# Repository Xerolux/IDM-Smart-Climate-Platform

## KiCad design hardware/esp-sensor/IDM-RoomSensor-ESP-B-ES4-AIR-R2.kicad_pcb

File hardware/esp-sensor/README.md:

# IDM Room Sensor ESP

The newest manufacturing revision is **B-ES5-MODULAR**, a 130 x 100 mm
four-layer engineering sample. It keeps ESP32-C6-N16, SHT45, USB-C, 24 V,
isolated RS-485, 0-10 V input/output, 1-Wire and contact inputs on the base and
moves CO2, VOC/NOx and pressure onto three universal 25 x 25 mm AIR-SLOT
modules. The symmetric 2x4 connector is electrically safe after 180-degree
rotation and each module has its own 3.3 V regulator.

**B-ES4-AIR-R2 Ultimate** is the all-sensors-fitted revision. It adds a
protected 6-32 VDC input rating, individually switchable LEDs and a
potential-free COM/NO/NC signal relay while retaining USB-C power/programming.
USB and external DC may be connected simultaneously through separate
Schottky OR-ing diodes. **B-ES5-MODULAR** remains intended for product tiers,
later upgrades and field-replaceable sensor modules.

Revision **B-ES2-C6** is the smaller baseline engineering
sample using an ESP32-C6-WROOM-1-N16, native USB-C, SHT45, MCP4725/OPA197
0-10 V output and isolated CA-IS3092W RS-485. It accepts protected 24 V field
power and USB power simultaneously through separate Schottky OR-ing diodes.

Revision **B-ES1** remains the simpler ESP32-C3-DevKitM-1 bench-test version.

## Order files

- B-ES5 complete package: `manufacturing/B-ES5-MODULAR/`
- B-ES5 PCB/schematic: `IDM-RoomSensor-ESP-B-ES5-MODULAR.kicad_pcb` and
  `IDM-RoomSensor-ESP-B-ES5-MODULAR.kicad_sch`
- B-ES5 AIR modules: `modules/`
- B-ES5 printable enclosure: `enclosure/B-ES5-MODULAR-PRINTING.md`
- B-ES4 Ultimate package: `manufacturing/B-ES4-AIR/`
- B-ES4 Ultimate R2 package: `manufacturing/B-ES4-AIR-R2/`
- B-ES3-C6 order instructions: `manufacturing/B-ES3-C6/README.md`
- B-ES3-C6 PCB source: `IDM-RoomSensor-ESP-B-ES3-C6.kicad_pcb`
- B-ES3-C6 schematic: `IDM-RoomSensor-ESP-B-ES3-C6.kicad_sch`
- B-ES3-C6 pin map: `B-ES3-C6-PINMAP.md`
- B-ES3-C6 printable enclosure: `enclosure/B-ES3-C6-PRINTING.md`
- B-ES2-C6 order instructions: `manufacturing/B-ES2-C6/README.md`
- B-ES2-C6 PCB source: `IDM-RoomSensor-ESP-B-ES2-C6.kicad_pcb`
- B-ES2-C6 schematic: `IDM-RoomSensor-ESP-B-ES2-C6.kicad_sch`
- B-ES2-C6 pin map: `B-ES2-C6-PINMAP.md`
- Next-revision hardware requirements: `B-ES3-TODO.md`
- B-ES1 legacy order package: `manufacturing/B-ES1/`

The original Rev-A files are incomplete design-history artifacts and must not
be sent to fabrication.

## Bring-up warning

These PCBs are not production-qualified. Flash and calibrate the ESP32 before
use. Start with a current-limited bench supply and dummy output load. Validate
all interface paths against the exact IDM model before connecting a heat pump.

IDM terminal assumption: 43 = KTY temperature signal, 42 = +14-32 V DC,
41 = common GND/KTY return and 40 = humidity 0-10 V. This assignment must be
confirmed on the target installation.

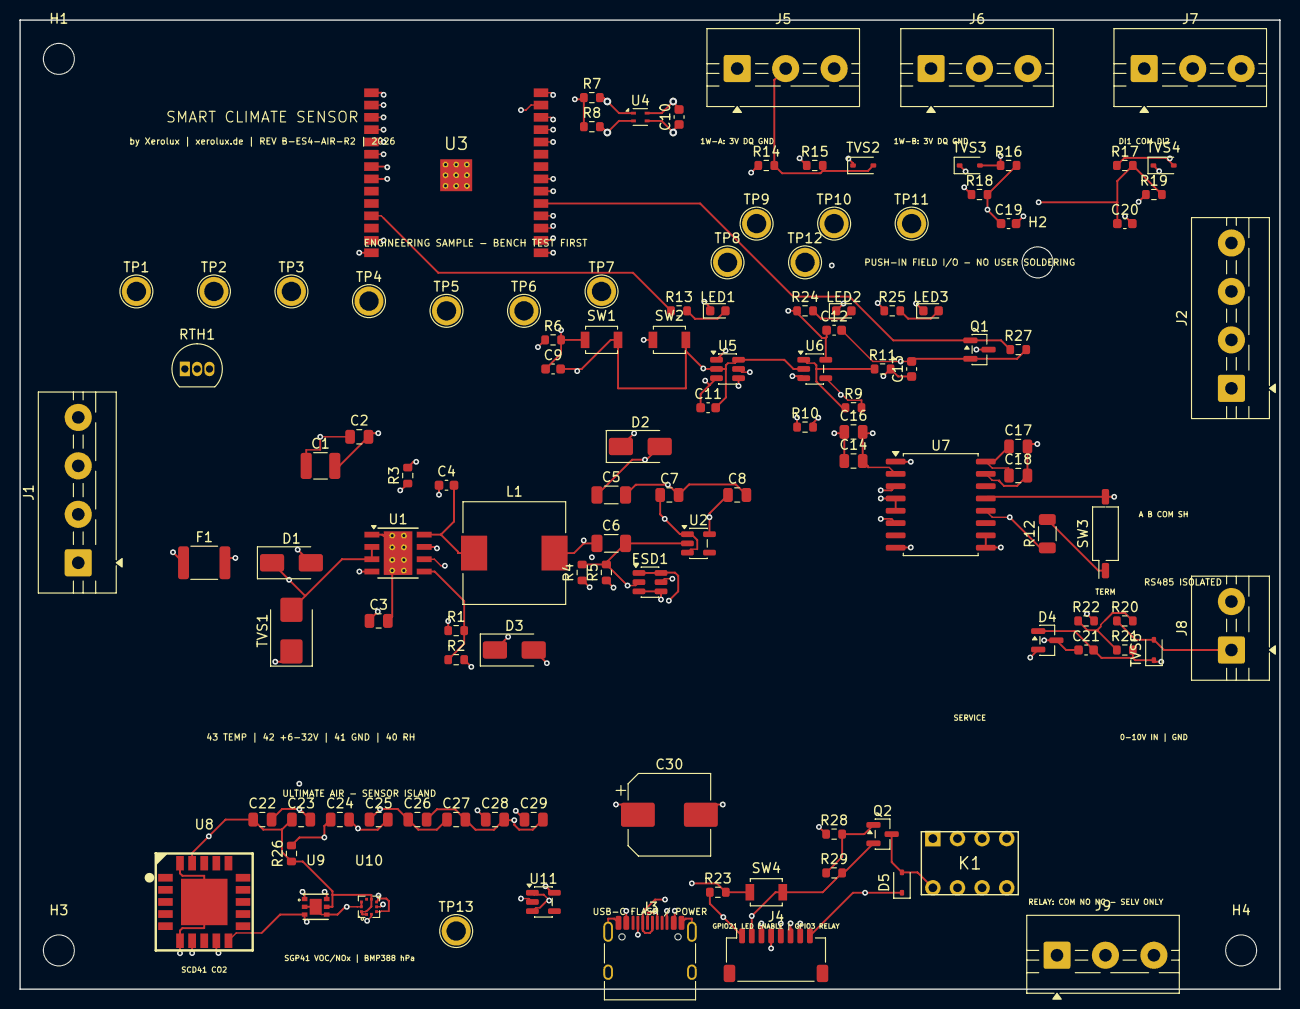
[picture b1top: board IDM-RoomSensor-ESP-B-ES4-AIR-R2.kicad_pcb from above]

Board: 4 copper layers, 130.0 x 100.0 mm, 119 parts (0 on the bottom side), 61 nets.

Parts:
C1: 4.7u 100V; C_1210_3225Metric
C2: 220n 100V; C_0805_2012Metric
C3, C24, C25: 1u; C_0805_2012Metric
C4, C10, C11, C19, C20, C21: 100n; C_0603_1608Metric
C5, C6: 47u; C_1206_3216Metric
C7, C16, C18, C28: 10u; C_0805_2012Metric
C8, C29: 22u; C_0805_2012Metric
C9: 1u; C_0603_1608Metric
C12, C13: 100n 50V; C_0603_1608Metric
C14, C17, C22, C26, C27: 100n; C_0805_2012Metric
C23: 4.7u; C_0805_2012Metric
C30: 220u 10V; CP_Elec_8x10
D1: SS16; D_SMA
D2, D3: SS14; D_SMA
D4: BAT54S; SOT-23
D5: 1N4148WS FLYBACK; D_SOD-323
ESD1: USBLC6-2SC6; SOT-23-6
F1: BSMD1812-050-60V; Fuse_1812_4532Metric
H1, H2, H3, H4: MountingHole_3.2mm_M3
J1: MX205R PUSH-IN 43/42/41/40; TerminalBlock_MaiXu_MX126-5.0-04P_1x04_P5.00mm
J2: MX205R PUSH-IN RS485 A/B/COM/SH; TerminalBlock_MaiXu_MX126-5.0-04P_1x04_P5.00mm
J3: USB-C; USB_C_Receptacle_HRO_TYPE-C-31-M-12
J4: EXPANSION; JST_SH_SM08B-SRSS-TB_1x08-1MP_P1.00mm_Horizontal
J5: 1WIRE A 3V/DQ/GND; TerminalBlock_MaiXu_MX126-5.0-03P_1x03_P5.00mm
J6: 1WIRE B 3V/DQ/GND; TerminalBlock_MaiXu_MX126-5.0-03P_1x03_P5.00mm
J7: CONTACT 1/COM/2; TerminalBlock_MaiXu_MX126-5.0-03P_1x03_P5.00mm
J8: 0-10V IN/GND; TerminalBlock_MaiXu_MX126-5.0-02P_1x02_P5.00mm
J9: RELAY COM/NO/NC; TerminalBlock_MaiXu_MX126-5.0-03P_1x03_P5.00mm
K1: HFD4/5; Relay_Hongfa_HFD4_DIP
L1: SRP1038A-330M; L_10.4x10.4_H4.8
LED1: STATUS; LED_0603_1608Metric
LED2: VIN; LED_0603_1608Metric
LED3: BUS GREEN; LED_0603_1608Metric
Q1: 2N7002 VIN LED; SOT-23
Q2: 2N7002 RELAY; SOT-23
R1, R3, R27, R29: 100k; R_0603_1608Metric
R2: 24.9k; R_0603_1608Metric
R4, R5: 5.1k; R_0603_1608Metric
R6, R10, R18, R19, R21, R23: 10k; R_0603_1608Metric
R7, R8, R15: 4.7k; R_0603_1608Metric
R9: 21k 1% CAL; R_0603_1608Metric
R11: 220R; R_0603_1608Metric
R12: 120R; R_1206_3216Metric
R13, R16, R17, R22, R25: 1k; R_0603_1608Metric
R14, R28: 100R; R_0603_1608Metric
R20: 33k; R_0603_1608Metric
R24: 18k; R_0603_1608Metric
R26: 10R; R_0603_1608Metric
RTH1: KTY81/210,112; TO-92_Inline
SW1: RESET; SW_SPST_B3U-1000P
SW2: BOOT; SW_SPST_B3U-1000P
SW3: TERM ON/OFF; SW_DIP_SPSTx01_Slide_Copal_CHS-01B_W7.62mm_P1.27mm
SW4: SERVICE; SW_SPST_B3U-1000P
TP1: 24V_RAW; TestPoint_Plated_Hole_D2.0mm
TP2: 24V_PROT; TestPoint_Plated_Hole_D2.0mm
TP3: SYS_5V; TestPoint_Plated_Hole_D2.0mm
TP4: +3V3; TestPoint_Plated_Hole_D2.0mm
TP5: I2C_SDA; TestPoint_Plated_Hole_D2.0mm
TP6: I2C_SCL; TestPoint_Plated_Hole_D2.0mm
TP7: RH_OUT; TestPoint_Plated_Hole_D2.0mm
TP8: TEMP_KTY; TestPoint_Plated_Hole_D2.0mm
TP9: RS485_A; TestPoint_Plated_Hole_D2.0mm
TP10: RS485_B; TestPoint_Plated_Hole_D2.0mm
TP11: RS485_COM; TestPoint_Plated_Hole_D2.0mm
TP12: GND; TestPoint_Plated_Hole_D2.0mm
TP13: AIR_3V3; TestPoint_Plated_Hole_D2.0mm
TVS1: SMBJ33A; D_SMB
TVS2, TVS3, TVS4: 3V3 ESD; D_SOD-323
TVS5: 12V ESD; D_SOD-323
U1: LMR36510ADDAR; TI_SO-PowerPAD-8_ThermalVias
U2: AP2112K-3.3; SOT-23-5
U3: ESP32-C6-WROOM-1-N8; ESP32-C6-WROOM-1
U4: SHT45; Sensirion_DFN-4_1.5x1.5mm_P0.8mm_SHT4x_NoCentralPad
U5: MCP4725A0T; SOT-23-6
U6: OPA197IDBVR; SOT-23-5
U7: CA-IS3092W; SOIC-16W_7.5x10.3mm_P1.27mm
U8: SCD41-D-R1; SENSOR-SMD_SCD41-D-R1
U9: SGP41-D-R4; DFN-6_L2.4-W2.4-P0.80-TL-EP
U10: BMP388; LGA-10_L2.0-W2.0-P0.50-BL
U11: AP2112K-3.3 AIR; SOT-23-5

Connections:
5V_BUCK: C5.1, C6.1, D2.2, L1.2, R1.1, R3.2
24V_FUSED: D1.2, F1.2
24V_PROT: C1.1, C2.1, C12.1, D1.1, R24.1, TP2.1, TVS1.2, U1.2, U1.3, U6.5
24V_RAW: F1.1, J1.2, TP1.1
+3V3: C8.1, C10.1, C11.1, C14.1, C16.1, D4.2, J4.1, J5.1, J6.1, R6.1, R7.1, R8.1, R15.1, R18.1, R19.1, R23.1, TP4.1, U2.5, U3.2, U4.3, U5.3, U7.1
ADC_0_10: C21.1, D4.3, R22.2, U3.8
AIN_0_10_RAW: J8.1, R20.1, TVS5.2
AIN_DIV: R20.2, R21.1, R22.1
AIR_3V3: C22.1, C23.1, C25.1, C26.1, C27.1, C29.1, R26.1, TP13.1, U8.7, U8.19, U9.5, U10.1, U10.6, U10.10, U11.5
BOOT: C4.1, U1.7
BUCK_FB: R1.2, R2.1, U1.5
BUS_LED: R25.1, U3.20
BUS_LED_R: LED3.2, R25.2
C6_BOOT: SW2.1, U3.15
C6_EN: C9.1, R6.2, SW1.1, U3.3
CONTACT1: C19.1, R16.2, R18.2, U3.16
CONTACT1_EXT: J7.1, R16.1, TVS3.2
CONTACT2: C20.1, R17.2, R19.2, U3.17
CONTACT2_EXT: J7.3, R17.1, TVS4.2
DAC_RAW: U5.1, U6.3
EXP_GPIO4: J4.6, U3.4
EXP_GPIO5: J4.7, U3.5
GND: C1.2, C2.2, C3.2, C5.2, C6.2, C7.2, C8.2, C9.2, C10.2, C11.2, C12.2, C13.2, C14.2, C16.2, C19.2, C20.2, C21.2, C22.2, C23.2, C24.2, C25.2, C26.2, C27.2, C28.2, C29.2, C30.2, D4.1, ESD1.2, J1.3, J3.A1, J3.A12, J3.B1, J3.B12, J3.SH, J4.2, J5.3, J6.3, J7.2, J8.2, LED1.1, LED3.1, Q1.2, Q2.2, R2.2, R4.2, R5.2, R10.2, R21.2, R27.2, R29.2, RTH1.2, SW1.2, SW2.2, SW4.2, TP12.1, TVS1.1, TVS2.1, TVS3.1, TVS4.1, TVS5.1, U1.1, U1.9, U2.2, U3.1, U3.28, U3.29, U4.4, U5.2, U5.6, U6.2, U7.2, U7.8, U8.6, U8.20, U8.21, U9.2, U9.4, U9.7, U10.3, U10.5, U10.8, U10.9, U11.2
I2C_SCL: J4.4, R8.2, TP6.1, U3.7, U4.2, U5.5, U8.9, U9.6, U10.2
I2C_SDA: J4.3, R7.2, TP5.1, U3.6, U4.1, U5.4, U8.10, U9.3, U10.4
ONEWIRE: J4.5, R14.1, U3.21
ONEWIRE_EXT: J5.2, J6.2, R14.2, R15.2, TVS2.2
OPAMP_FB: R9.2, R10.1, U6.4
OPAMP_OUT: R9.1, R11.1, U6.1
PWR24_LED_R: LED2.2, R24.2
PWR_GOOD: R3.1, U1.4
PWR_LED_EN: Q1.1, R27.1, U3.19
PWR_LED_K: LED2.1, Q1.3
RELAY_COIL_L: D5.2, K1.8, Q2.3
RELAY_COM: J9.1, K1.3
RELAY_CTRL: R28.1, U3.26
RELAY_GATE: Q2.1, R28.2, R29.1
RELAY_NC: J9.3, K1.2
RELAY_NO: J9.2, K1.4
RH_OUT: C13.1, J1.4, R11.2, TP7.1
RS485_A: J2.1, R12.1, TP9.1, U7.12
RS485_B: J2.2, SW3.2, TP10.1, U7.13
RS485_COM: C17.2, C18.2, J2.3, TP11.1, U7.9, U7.10, U7.15
RS485_DE: U3.27, U7.4, U7.5
RS485_RX: U3.24, U7.3
RS485_TERM: R12.2, SW3.1
RS485_TX: U3.25, U7.6
SERVICE_BUTTON: R23.2, SW4.1, U3.18
SGP_VDD: C24.1, R26.2, U9.1
STATUS_LED: R13.1, U3.11
STATUS_LED_R: LED1.2, R13.2
SW: C4.2, L1.1, U1.8
SYS_5V: C7.1, C28.1, C30.1, D2.1, D3.1, D5.1, J4.8, K1.1, TP3.1, U2.1, U2.3, U11.1, U11.3
TEMP_KTY: J1.1, RTH1.1, TP8.1
USB_5V: D3.2, ESD1.5, J3.A4, J3.A9, J3.B4, J3.B9
USB_CC1: J3.A5, R4.1
USB_CC2: J3.B5, R5.1
USB_D+: ESD1.3, ESD1.4, J3.A6, J3.B6, U3.14
USB_D-: ESD1.1, ESD1.6, J3.A7, J3.B7, U3.13
VCC_BYP: C3.1, U1.6
VISO: C17.1, C18.1, U7.16

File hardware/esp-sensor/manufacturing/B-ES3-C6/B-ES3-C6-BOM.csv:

Designator,Quantity,Manufacturer,Manufacturer Part Number,Description,Footprint,LCSC Part Number,Assembly
"J1,J2",2,MAX,MX205R-5.0-04P-GN01-Cu-A,4-way push-in spring terminal,THT P5.00mm 1x04,C7471336,JLCPCB Standard PCBA
RTH1,1,NXP,"KTY81/210,112",2 kohm silicon temperature sensor,TO-92 inline,C481813,JLCPCB Standard PCBA
F1,1,Littelfuse,1812L050/30PR,500 mA hold 30 V resettable fuse,1812,C151168,JLCPCB Standard PCBA
D1,1,Zhengxin,SS16,1 A 60 V Schottky,SMA,C5262487,JLCPCB Standard PCBA
TVS1,1,MDD,SMBJ33A,33 V 600 W unidirectional TVS,SMB,C173526,JLCPCB Standard PCBA
U1,1,Texas Instruments,LMR36510ADDAR,65 V 1 A synchronous buck,SOP-8-EP,C1858393,JLCPCB Standard PCBA
L1,1,Bourns,SRP1038A-330M,33 uH 3.5 A shielded inductor,11x10 mm SMD,C2041318,JLCPCB Standard PCBA
"R1,R3",2,UNI-ROYAL,0603WAF1003T5E,100 kohm 1%,0603,C25803,JLCPCB Standard PCBA
R2,1,UNI-ROYAL,0603WAF2492T5E,24.9 kohm 1%,0603,C25962,JLCPCB Standard PCBA
C1,1,JLCPCB Assembly,4.7uF/100V,4.7 uF 100 V MLCC,1210,C9900085220,JLCPCB Standard PCBA
C2,1,CCTC,TCC0805X7R224K101FT,220 nF 100 V X7R 10%,0805,C2994652,JLCPCB Standard PCBA
C3,1,Samsung Electro-Mechanics,CL21B105KBFNNNE,1 uF 50 V X7R,0805,C28323,JLCPCB Standard PCBA
"C4,C10,C11,C12,C13",5,Murata,GRM188R71H104KA93D,100 nF 50 V X7R,0603,C77055,JLCPCB Standard PCBA
"C5,C6",2,Samsung Electro-Mechanics,CL31A476MPHNNNE,47 uF 10 V X5R,1206,C96123,JLCPCB Standard PCBA
"D2,D3",2,JSMSEMI,SS14,1 A 40 V Schottky power OR diode,SMA,C2837270,JLCPCB Standard PCBA
U2,1,TECH PUBLIC,AP2112K-3.3TRG1,3.3 V 600 mA LDO,SOT-23-5,C23380830,JLCPCB Standard PCBA
"C7,C16,C18",3,Murata,GRM21BR71A106KE51L,10 uF 10 V X7R,0805,C86038,JLCPCB Standard PCBA
C8,1,TDK,C2012X5R1A226MT0J0E,22 uF 10 V X5R,0805,C361180,JLCPCB Standard PCBA
U3,1,Espressif Systems,ESP32-C6-WROOM-1-N16,Wi-Fi 6/BLE/Thread module 16 MB flash,LCC-LGA 18x25.5 mm,C5445014,JLCPCB Standard PCBA
J3,1,Korean Hroparts,TYPE-C-31-M-12,USB-C USB2 receptacle,SMD/THT shield,C165948,JLCPCB Standard PCBA
ESD1,1,TECH PUBLIC,USBLC6-2SC6,USB dual-line ESD protection,SOT-23-6,C2827654,JLCPCB Standard PCBA
"R4,R5",2,UNI-ROYAL,0603WAF5101T5E,5.1 kohm 1% USB-C CC,0603,C23186,JLCPCB Standard PCBA
R6,1,UNI-ROYAL,0603WAF1002T5E,10 kohm 1%,0603,C25804,JLCPCB Standard PCBA
C9,1,Samsung Electro-Mechanics,CL10A105KB8NNNC,1 uF 50 V X5R,0603,C15849,JLCPCB Standard PCBA
"SW1,SW2",2,Omron,B3U-1000P,momentary tactile switch,SMD,C231329,JLCPCB Standard PCBA
U4,1,Sensirion,SHT45-AD1B-R2,temperature and humidity sensor,DFN-4 1.5x1.5 mm,C5221601,JLCPCB Standard PCBA
"R7,R8",2,Yageo,RC0603FR-074K7L,4.7 kohm 1%,0603,C99782,JLCPCB Standard PCBA
U5,1,Microchip,MCP4725A0T-E/CH,12-bit I2C DAC,SOT-23-6,C144198,JLCPCB Standard PCBA
U6,1,Texas Instruments,OPA197IDBVR,36 V precision rail-to-rail op amp,SOT-23-5,C221351,JLCPCB Standard PCBA
R9,1,TyoHM,RMC060321K1%N,21 kohm 1%; calibrated gain headroom,0603,C269418,JLCPCB Standard PCBA
R10,1,Yageo,RT0603BRD0710KL,10 kohm 0.1% thin film,0603,C95204,JLCPCB Standard PCBA
R11,1,Yageo,RC0603FR-07220RL,220 ohm 1%,0603,C107696,JLCPCB Standard PCBA
U7,1,Chipanalog,CA-IS3092W,isolated 500 kbps RS-485 with integrated isolated power,SOIC-16W,C2890051,JLCPCB Standard PCBA
"C14,C17",2,Samsung Electro-Mechanics,CL21B104KBCNNNC,100 nF 50 V X7R,0805,C49678,JLCPCB Standard PCBA
R12,1,Yageo,RC1206FR-07120RL,120 ohm 1% RS-485 termination,1206,C114928,JLCPCB Standard PCBA
J4,1,JST,SM08B-SRSS-TB(LF)(SN),8-way 1 mm expansion connector,SMD right angle,C160407,JLCPCB Standard PCBA
LED1,1,MEIHUA,MHT192CGCT,green status LED,0603,C389518,JLCPCB Standard PCBA
R13,1,Yageo,RC0603FR-071KL,1 kohm 1%,0603,C21190,JLCPCB Standard PCBA
SW3,1,BIWIN,SOP01,user-accessible RS-485 termination switch,SMD DIP SPST,C3294660,JLCPCB Standard PCBA
"J5,J6,J7",3,MAX,MX205R-5.0-03P-GN01-Cu-A,3-way push-in spring terminal,THT P5.00mm 1x03,C7471335,JLCPCB Standard PCBA
J8,1,MAX,MX205R-5.0-02P-GN01-Cu-A,2-way push-in spring terminal,THT P5.00mm 1x02,C7471334,JLCPCB Standard PCBA
R14,1,UNI-ROYAL,0603WAF1000T5E,100 ohm 1% 1-Wire series resistor,0603,C22775,JLCPCB Standard PCBA
R15,1,Yageo,RC0603FR-074K7L,4.7 kohm 1% 1-Wire pull-up,0603,C99782,JLCPCB Standard PCBA
"TVS2,TVS3,TVS4",3,TECH PUBLIC,PCESD3V3D3,3.3 V field-interface ESD protection,SOD-323,C2928727,JLCPCB Standard PCBA
"R16,R17,R22,R25",4,UNI-ROYAL,0603WAF1001T5E,1 kohm 1%,0603,C21190,JLCPCB Standard PCBA
"R18,R19,R21,R23",4,UNI-ROYAL,0603WAF1002T5E,10 kohm 1%,0603,C25804,JLCPCB Standard PCBA
"C19,C20,C21",3,Murata,GRM188R71H104KA93D,100 nF 50 V X7R,0603,C77055,JLCPCB Standard PCBA
TVS5,1,ElecSuper,PESD12VL1BA-ES,12 V bidirectional 0-10 V input protection,SOD-323,C5180221,JLCPCB Standard PCBA
R20,1,UNI-ROYAL,0603WAF3302T5E,33 kohm 1% 0-10 V divider,0603,C4216,JLCPCB Standard PCBA
D4,1,IDCHIP,BAT54S,dual Schottky ADC rail clamp,SOT-23,C2848194,JLCPCB Standard PCBA
SW4,1,Omron,B3U-1000P,service and identify button,SMD,C231329,JLCPCB Standard PCBA
R24,1,UNI-ROYAL,0603WAF1202T5E,12 kohm 1% 24 V LED resistor,0603,C22790,JLCPCB Standard PCBA
"LED2,LED3",2,MEIHUA,MHT192CGCT,green diagnostic LED,0603,C389518,JLCPCB Standard PCBA

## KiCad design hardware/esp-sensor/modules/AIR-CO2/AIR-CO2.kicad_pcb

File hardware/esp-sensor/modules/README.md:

# Xerolux AIR-SLOT modules

B-ES5-MODULAR uses three electrically identical 2x4, 2.54 mm slots. The base
board is labelled CO2, VOC/NOx and PRESSURE for a clear default arrangement,
but every module works in every slot. Up to three modules may be fitted at the
same time.

## Rotation-safe pinout

| Pins | Signal | Purpose |
|---|---|---|
| 1 and 8 | GND | ground |
| 2 and 7 | SLOT_5V | protected system 5 V |
| 3 and 6 | I2C_SDA | shared I2C data |
| 4 and 5 | I2C_SCL | shared I2C clock |

The symmetric pinout is electrically identical after a 180-degree rotation.
Each module produces its own 3.3 V locally. For the enclosure, insert all
modules with their sensor side toward the broad lid ventilation field; the
electrical protection is not a substitute for correct mechanical orientation.

## Available modules

- AIR-CO2: Sensirion SCD41, address 0x62
- AIR-VOCNOX: Sensirion SGP41, address 0x59
- AIR-PRESSURE: Bosch BMP390, address 0x76

All modules are 25 x 25 mm, four-layer boards. Four layers are intentional:
the four duplicated signal pairs are routed independently without jumpers,
making the connector truly rotation-safe.

The female socket is a JLCPCB wave-solder part. Its stock and minimum purchase
quantity are dynamic; verify C58378 in the assembly viewer before payment.

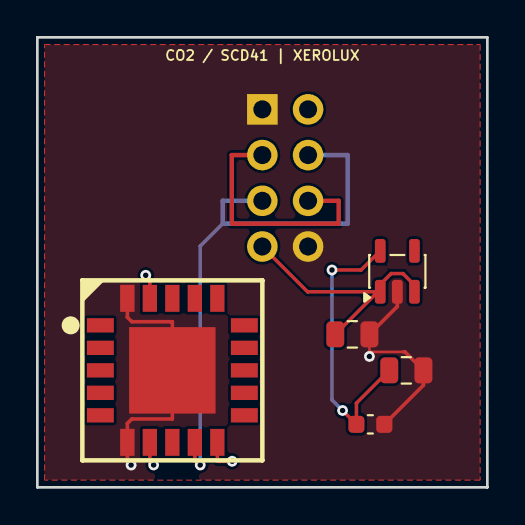
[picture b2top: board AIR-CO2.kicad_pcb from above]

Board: 4 copper layers, 25.0 x 25.0 mm, 6 parts (1 on the bottom side), 5 nets.

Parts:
C1: 10u; C_0805_2012Metric
C2: 22u; C_0805_2012Metric
C3: 100n; C_0603_1608Metric
J1: AIR-SLOT; PinSocket_2x04_P2.54mm_Vertical
U1: SCD41-D-R1; SENSOR-SMD_SCD41-D-R1
U2: AP2112K-3.3; SOT-23-5

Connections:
GND: C1.2, C2.2, C3.2, J1.1, J1.8, U1.6, U1.20, U1.21, U2.2
I2C_SCL: J1.4, J1.5, U1.9
I2C_SDA: J1.3, J1.6, U1.10
MOD_3V3: C2.1, C3.1, U1.7, U1.19, U2.5
SLOT_5V: C1.1, J1.2, J1.7, U2.1, U2.3

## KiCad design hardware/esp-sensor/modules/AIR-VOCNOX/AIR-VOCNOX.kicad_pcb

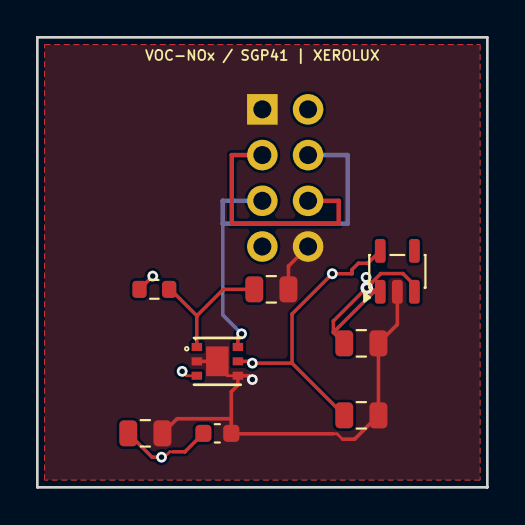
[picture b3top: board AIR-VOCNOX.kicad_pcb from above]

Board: 4 copper layers, 25.0 x 25.0 mm, 9 parts (1 on the bottom side), 6 nets.

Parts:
C1, C2: 1u; C_0805_2012Metric
C3: 100n; C_0603_1608Metric
C4: 10u; C_0805_2012Metric
C5: 22u; C_0805_2012Metric
J1: AIR-SLOT; PinSocket_2x04_P2.54mm_Vertical
R1: 10R; R_0603_1608Metric
U1: SGP41-D-R4; DFN-6_L2.4-W2.4-P0.80-TL-EP
U2: AP2112K-3.3; SOT-23-5

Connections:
GND: C1.2, C2.2, C3.2, C4.2, C5.2, J1.1, J1.8, U1.2, U1.4, U1.7, U2.2
I2C_SCL: J1.4, J1.5, U1.6
I2C_SDA: J1.3, J1.6, U1.3
MOD_3V3: C2.1, C3.1, C5.1, R1.1, U1.5, U2.5
SGP_VDD: C1.1, R1.2, U1.1
SLOT_5V: C4.1, J1.2, J1.7, U2.1, U2.3

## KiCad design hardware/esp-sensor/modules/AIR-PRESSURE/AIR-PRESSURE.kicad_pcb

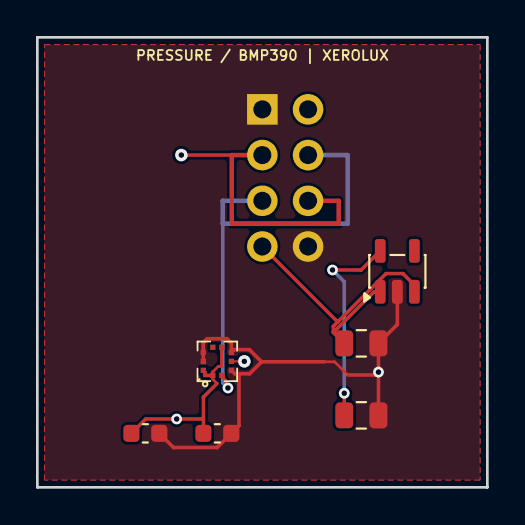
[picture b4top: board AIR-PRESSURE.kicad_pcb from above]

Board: 4 copper layers, 25.0 x 25.0 mm, 7 parts (1 on the bottom side), 5 nets.

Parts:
C1, C2: 100n; C_0603_1608Metric
C3: 10u; C_0805_2012Metric
C4: 22u; C_0805_2012Metric
J1: AIR-SLOT; PinSocket_2x04_P2.54mm_Vertical
U1: BMP390; LGA-10_L2.0-W2.0-P0.50-BL
U2: AP2112K-3.3; SOT-23-5

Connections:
GND: C1.2, C2.2, C3.2, C4.2, J1.1, J1.8, U1.3, U1.5, U1.8, U1.9, U2.2
I2C_SCL: J1.4, J1.5, U1.2
I2C_SDA: J1.3, J1.6, U1.4
MOD_3V3: C1.1, C2.1, C4.1, U1.1, U1.6, U1.10, U2.5
SLOT_5V: C3.1, J1.2, J1.7, U2.1, U2.3

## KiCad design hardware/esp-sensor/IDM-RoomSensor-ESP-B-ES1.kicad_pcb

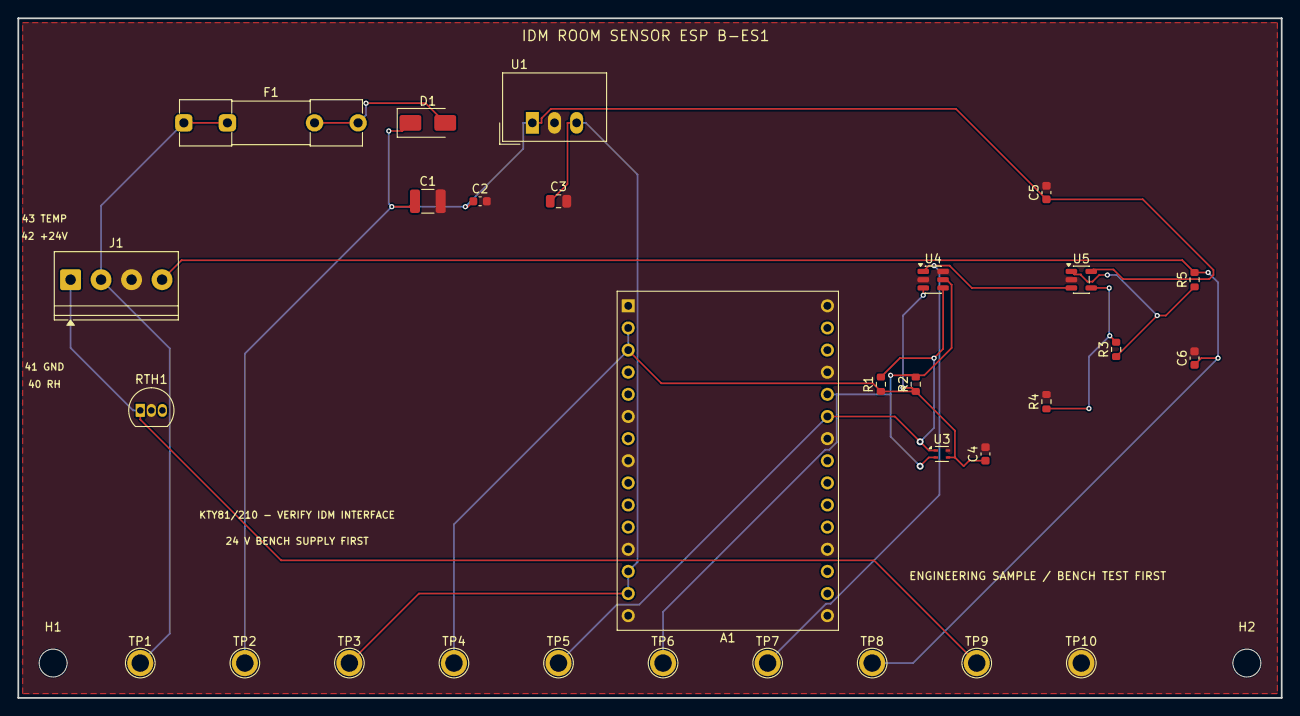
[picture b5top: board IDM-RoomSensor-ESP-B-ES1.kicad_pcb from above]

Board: 2 copper layers, 145.0 x 78.0 mm, 32 parts (0 on the bottom side), 13 nets.

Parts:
A1: ESP32-C3-DevKitM-1
C1: 22u 50V; C_1210_3225Metric
C2, C5, C6: 100n 50V; C_0603_1608Metric
C3: 10u 10V; C_0805_2012Metric
C4: 100n 16V; C_0603_1608Metric
D1: SS16-E3/61T; D_SMA
F1: 500mA 5x20mm; Fuseholder_Clip-5x20mm_Littelfuse_111_Inline_P20.00x5.00mm_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
H1, H2: M3; MountingHole_3.2mm_M3
J1: IDM / BENCH; TerminalBlock_Phoenix_PT-1,5-4-3.5-H_1x04_P3.50mm_Horizontal
R1, R2: 4.7k; R_0603_1608Metric
R3: 20.3k 0.1%; R_0603_1608Metric
R4: 10k 0.1%; R_0603_1608Metric
R5: 220R 1%; R_0603_1608Metric
RTH1: KTY81/210; TO-92_Inline
TP1: 24V_RAW; TestPoint_Plated_Hole_D2.0mm
TP2: 24V_PROT; TestPoint_Plated_Hole_D2.0mm
TP3: +5V; TestPoint_Plated_Hole_D2.0mm
TP4: +3V3; TestPoint_Plated_Hole_D2.0mm
TP5: I2C_SDA; TestPoint_Plated_Hole_D2.0mm
TP6: I2C_SCL; TestPoint_Plated_Hole_D2.0mm
TP7: DAC_RAW; TestPoint_Plated_Hole_D2.0mm
TP8: RH_OUT; TestPoint_Plated_Hole_D2.0mm
TP9: TEMP_KTY; TestPoint_Plated_Hole_D2.0mm
TP10: GND; TestPoint_Plated_Hole_D2.0mm
U1: TSR 1-2450; Converter_DCDC_TRACO_TSR-1_THT
U3: SHT45-AD1B-R2; Sensirion_DFN-4_1.5x1.5mm_P0.8mm_SHT4x_NoCentralPad
U4: MCP4725A0T-E/CH; SOT-23-6
U5: OPA197IDBVR; SOT-23-5

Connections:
24V_FUSED: D1.2, F1.2
24V_PROT: C1.1, C2.1, C5.1, D1.1, TP2.1, U1.1, U5.5
24V_RAW: F1.1, J1.2, TP1.1
+3V3: A1.2, A1.3, C4.1, R1.1, R2.1, TP4.1, U3.3, U4.3
+5V: A1.13, A1.14, C3.1, TP3.1, U1.3
DAC_RAW: TP7.1, U4.1, U5.3
GND: A1.1, A1.6, A1.8, A1.12, A1.15, A1.16, A1.19, A1.24, A1.27, A1.30, C1.2, C2.2, C3.2, C4.2, C5.2, C6.2, J1.3, R4.2, RTH1.2, TP10.1, U1.2, U3.4, U4.2, U4.6, U5.2
I2C_SCL: A1.26, R2.2, TP6.1, U3.2, U4.5
I2C_SDA: A1.25, R1.2, TP5.1, U3.1, U4.4
OPAMP_FB: R3.2, R4.1, U5.4
OPAMP_OUT: R3.1, R5.1, U5.1
RH_OUT: C6.1, J1.4, R5.2, TP8.1
TEMP_KTY: J1.1, RTH1.1, TP9.1

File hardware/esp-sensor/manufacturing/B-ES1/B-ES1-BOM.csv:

Designator,Quantity,Manufacturer,Manufacturer Part Number,Description,Footprint,Assembly,Status
PCB1,1,Custom,IDM-RoomSensor-ESP-B-ES1,2-layer engineering sample PCB 145x78mm,,PCB fab,Order Gerber ZIP
J1,1,Phoenix Contact,1984633,PT 1.5/4-3.5-H 4-position terminal block,PT-1.5-4-3.5-H THT,Hand,Required
F1 clips,2,Littelfuse,111,5x20mm PCB fuse clips,20mm clip spacing THT,Hand,Required
F1 fuse,1,Littelfuse,0218.500MXP,500mA 250V time-lag fuse,5x20mm,Hand,Required
D1,1,Vishay,SS16-E3/61T,1A 60V Schottky diode,SMA,SMT,Required
U1,1,Traco Power,TSR 1-2450,6.5-36V input 5V 1A switching regulator,TSR-1 SIP3,Hand,Required
A1,1,Espressif,ESP32-C3-DevKitM-1,ESP32-C3 development board,2x15 THT module,Hand,Required
U3,1,Sensirion,SHT45-AD1B-R2,Digital humidity and temperature sensor,DFN-4 1.5x1.5mm,SMT,Required
U4,1,Microchip,MCP4725A0T-E/CH,12-bit I2C DAC,SOT-23-6,SMT,Required
U5,1,Texas Instruments,OPA197IDBVR,36V precision rail-to-rail op amp,SOT-23-5,SMT,Required
RTH1,1,NXP,"KTY81/210,112",Silicon temperature sensor 2k at 25C,SOD70 / TO-92 inline,Hand,Obsolete - source verified stock and verify IDM characteristic
R1 R2,2,Yageo,RC0603FR-074K7L,4.7k 1% resistor,0603,SMT,Required
R3,1,Panasonic,ERA-3AEB2032V,20.3k 0.1% thin-film resistor,0603,SMT,Required
R4,1,Panasonic,ERA-3AEB103V,10k 0.1% thin-film resistor,0603,SMT,Required
R5,1,Yageo,RC0603FR-07220RL,220 ohm 1% resistor,0603,SMT,Required
C1,1,Murata,GRM32ER71H226KE15L,22uF 50V X7R capacitor,1210,SMT,Required
C2 C5 C6,3,Murata,GRM188R71H104KA93D,100nF 50V X7R capacitor,0603,SMT,Required
C3,1,Murata,GRM21BR71A106KE51L,10uF 10V X7R capacitor,0805,SMT,Required
C4,1,Murata,GRM188R71C104KA01D,100nF 16V X7R capacitor,0603,SMT,Required
TP1-TP10,10,Generic,DNP-wire-loop,Optional plated-hole test loops,2.0mm plated hole,Hand,Optional
H1 H2,2,Generic,M3 hardware,M3 mounting screws and spacers,3.2mm NPTH,Mechanical,Optional

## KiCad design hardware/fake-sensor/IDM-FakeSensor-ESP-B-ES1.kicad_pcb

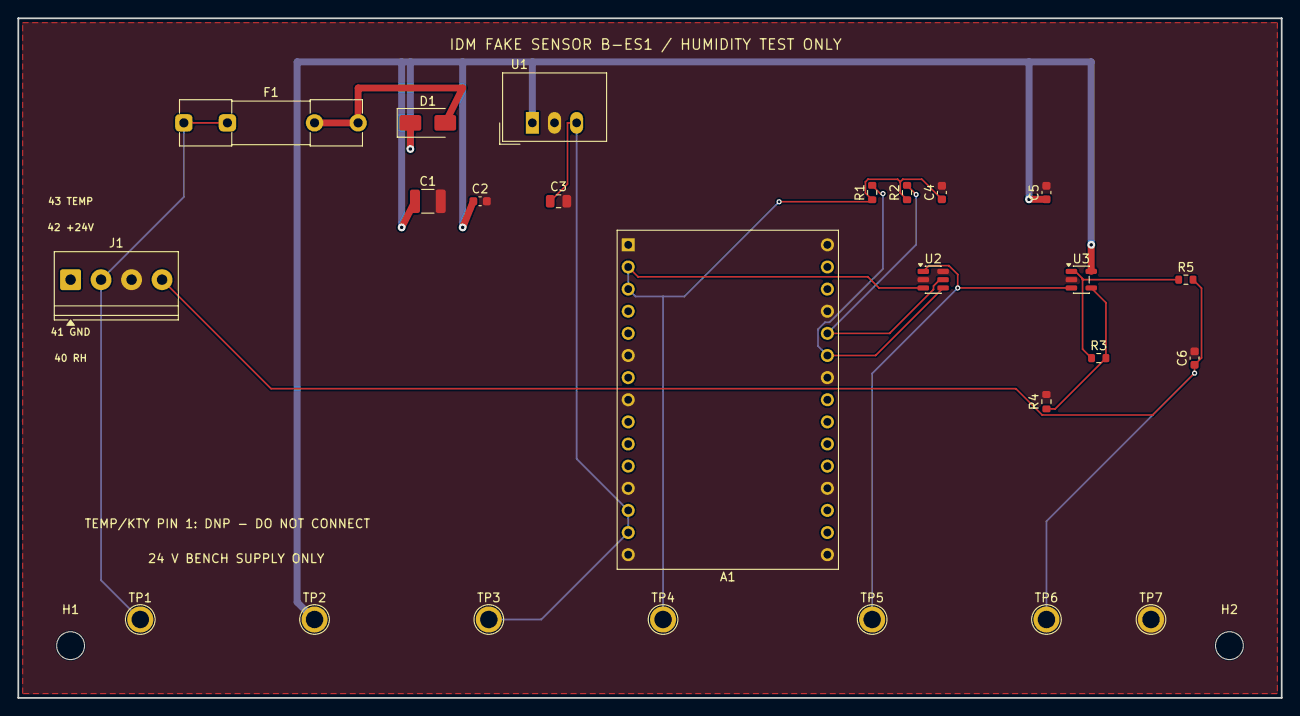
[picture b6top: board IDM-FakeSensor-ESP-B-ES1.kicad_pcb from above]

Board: 2 copper layers, 145.0 x 78.0 mm, 27 parts (0 on the bottom side), 12 nets.

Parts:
A1: ESP32-C3-DevKitM-1
C1: 22u 50V; C_1210_3225Metric
C2, C5, C6: 100n 50V; C_0603_1608Metric
C3: 10u 10V; C_0805_2012Metric
C4: 100n 16V; C_0603_1608Metric
D1: SS16-E3/61T; D_SMA
F1: 500mA 5x20mm; Fuseholder_Clip-5x20mm_Littelfuse_111_Inline_P20.00x5.00mm_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
H1, H2: MountingHole_3.2mm_M3
J1: IDM / BENCH; TerminalBlock_Phoenix_PT-1,5-4-3.5-H_1x04_P3.50mm_Horizontal
R1, R2: 4.7k; R_0603_1608Metric
R3: 20.3k 0.1%; R_0603_1608Metric
R4: 10k 0.1%; R_0603_1608Metric
R5: 220R; R_0603_1608Metric
TP1: 24V_RAW; TestPoint_Plated_Hole_D2.0mm
TP2: 24V_PROT; TestPoint_Plated_Hole_D2.0mm
TP3: +5V; TestPoint_Plated_Hole_D2.0mm
TP4: +3V3; TestPoint_Plated_Hole_D2.0mm
TP5: DAC_RAW; TestPoint_Plated_Hole_D2.0mm
TP6: RH_OUT; TestPoint_Plated_Hole_D2.0mm
TP7: GND; TestPoint_Plated_Hole_D2.0mm
U1: TSR 1-2450; Converter_DCDC_TRACO_TSR-1_THT
U2: MCP4725A0T-E/CH; SOT-23-6
U3: OPA197IDBVR; SOT-23-5

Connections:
24V_FUSED: D1.2, F1.2
24V_PROT: C1.1, C2.1, C5.1, D1.1, TP2.1, U1.1, U3.5
24V_RAW: F1.1, J1.2, TP1.1
+3V3: A1.2, A1.3, C4.1, R1.1, R2.1, TP4.1, U2.3
+5V: A1.13, A1.14, C3.1, TP3.1, U1.3
DAC_RAW: TP5.1, U2.1, U3.3
GND: A1.1, A1.6, A1.8, A1.12, A1.15, A1.16, A1.19, A1.24, A1.27, A1.30, C1.2, C2.2, C3.2, C4.2, C5.2, C6.2, J1.3, R4.2, TP7.1, U1.2, U2.2, U2.6, U3.2
I2C_SCL: A1.26, R2.2, U2.5
I2C_SDA: A1.25, R1.2, U2.4
OPAMP_FB: R3.2, R4.1, U3.4
OPAMP_OUT: R3.1, R5.1, U3.1
RH_OUT: C6.1, J1.4, R5.2, TP6.1

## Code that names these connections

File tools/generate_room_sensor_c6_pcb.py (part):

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    b=pcbnew.BOARD(); b.SetCopperLayerCount(4); add_outline(b,right,bottom)
    names=["GND","24V_RAW","24V_FUSED","24V_PROT","PWR_GOOD","BUCK_FB","VCC_BYP","BOOT","SW","5V_BUCK","USB_5V","SYS_5V","+3V3",
           "TEMP_KTY","RH_OUT","DAC_RAW","OPAMP_OUT","OPAMP_FB","I2C_SDA","I2C_SCL","C6_EN","C6_BOOT","USB_D-","USB_D+","USB_CC1","USB_CC2",
           "STATUS_LED","STATUS_LED_R","ONEWIRE","EXP_GPIO4","EXP_GPIO5","RS485_RX","RS485_TX","RS485_DE","VISO","RS485_A","RS485_B","RS485_COM","RS485_SHIELD","RS485_TERM"]
    if extended:
        names += ["ONEWIRE_EXT","CONTACT1","CONTACT2","CONTACT1_EXT","CONTACT2_EXT","SERVICE_BUTTON",
                  "BUS_LED","BUS_LED_R","PWR24_LED_R","AIN_0_10_RAW","AIN_DIV","ADC_0_10"]
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    p("D2","SS14","Diode_SMD","D_SMA",74,54,0,{1:"SYS_5V",2:"5V_BUCK"}); p("D3","SS14","Diode_SMD","D_SMA",61,75,0,{1:"SYS_5V",2:"USB_5V"})
    p("U2","AP2112K-3.3","Package_TO_SOT_SMD","SOT-23-5",80,64,0,{1:"SYS_5V",2:"GND",3:"SYS_5V",5:"+3V3"})
    p("C7","10u","Capacitor_SMD","C_0805_2012Metric",77,59,0,{1:"SYS_5V",2:"GND"}); p("C8","22u","Capacitor_SMD","C_0805_2012Metric",84,59,0,{1:"+3V3",2:"GND"})
    c6={1:"GND",2:"+3V3",3:"C6_EN",4:"EXP_GPIO4",5:"EXP_GPIO5",6:"I2C_SDA",7:"I2C_SCL",10:"STATUS_LED",13:"USB_D-",14:"USB_D+",15:"C6_BOOT",21:"ONEWIRE",24:"RS485_RX",25:"RS485_TX",27:"RS485_DE",28:"GND",29:"GND"}
    if extended: c6.update({8:"ADC_0_10",16:"CONTACT1",17:"CONTACT2",18:"SERVICE_BUTTON",20:"BUS_LED"})
    if air_r2:
        c6.pop(10)
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    p("R9","21k 1% CAL","Resistor_SMD","R_0603_1608Metric",96,50,0,{1:"OPAMP_OUT",2:"OPAMP_FB"}); p("R10","10k","Resistor_SMD","R_0603_1608Metric",91,52,0,{1:"OPAMP_FB",2:"GND"}); p("R11","220R","Resistor_SMD","R_0603_1608Metric",99,46,0,{1:"OPAMP_OUT",2:"RH_OUT"})
    p("C11","100n","Capacitor_SMD","C_0603_1608Metric",81,50,0,{1:"+3V3",2:"GND"}); p("C12","100n 50V","Capacitor_SMD","C_0603_1608Metric",94,42,0,{1:"24V_PROT",2:"GND"}); p("C13","100n 50V","Capacitor_SMD","C_0603_1608Metric",102,46,90,{1:"RH_OUT",2:"GND"})
    p("U7","CA-IS3092W","Package_SO","SOIC-16W_7.5x10.3mm_P1.27mm",105,60,0,{1:"+3V3",2:"GND",3:"RS485_RX",4:"RS485_DE",5:"RS485_DE",6:"RS485_TX",8:"GND",9:"RS485_COM",10:"RS485_COM",12:"RS485_A",13:"RS485_B",15:"RS485_COM",16:"VISO"})
    for ref,val,x,y,pins in [("C14","100n",96,55.5,{1:"+3V3",2:"GND"}),("C16","10u",96,52.5,{1:"+3V3",2:"GND"}),("C17","100n",113,54,{1:"VISO",2:"RS485_COM"}),("C18","10u",113,57,{1:"VISO",2:"RS485_COM"})]: p(ref,val,"Capacitor_SMD","C_0805_2012Metric",x,y,0,pins)
    p("J2","MX205R PUSH-IN RS485 A/B/COM/SH" if extended else "RS485 A/B/COM/SH",term_lib,term(4),135 if extended else 115,48 if extended else 43,90,{1:"RS485_A",2:"RS485_B",3:"RS485_COM",4:"RS485_SHIELD"})
    p("R12","120R","Resistor_SMD","R_1206_3216Metric",116,63,90,{1:"RS485_A",2:"RS485_TERM"})
    if extended: p("SW3","TERM ON/OFF","Button_Switch_SMD","SW_DIP_SPSTx01_Slide_Copal_CHS-01B_W7.62mm_P1.27mm",122,63,90,{1:"RS485_TERM",2:"RS485_B"})
    else: p("JP1","TERM","Jumper","SolderJumper-2_P1.3mm_Open_Pad1.0x1.5mm",116,63,90,{1:"RS485_TERM",2:"RS485_B"})
    p("J4","EXPANSION","Connector_JST","JST_SH_SM08B-SRSS-TB_1x08-1MP_P1.00mm_Horizontal",119 if modular else 88,106.5 if tall else (86.5 if extended else 76.5),0,{1:"+3V3",2:"GND",3:"I2C_SDA",4:"I2C_SCL",5:"ONEWIRE",6:"EXP_GPIO4",7:"EXP_GPIO5",8:"SYS_5V"})
    p("LED1","STATUS","LED_SMD","LED_0603_1608Metric",82,40,0,{1:"GND",2:"STATUS_LED_R"} if air_r2 else {1:"STATUS_LED_R",2:"GND"}); p("R13","1k","Resistor_SMD","R_0603_1608Metric",78,40,0,{1:"STATUS_LED",2:"STATUS_LED_R"})
    if extended:
        p("J5","1WIRE A 3V/DQ/GND",term_lib,term(3),84,15,0,{1:"+3V3",2:"ONEWIRE_EXT",3:"GND"})
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        p("C30","220u 10V","Capacitor_SMD","CP_Elec_8x10",77 if air_r2 else 126,92 if air_r2 else 99,0,{1:"SYS_5V",2:"GND"})
        p("TP13","AIR_3V3","TestPoint","TestPoint_Plated_Hole_D2.0mm",55,104,0,{1:"AIR_3V3"})
    if modular:
        slot_pins={1:"GND",2:"SYS_5V",3:"I2C_SDA",4:"I2C_SCL",5:"I2C_SCL",6:"I2C_SDA",7:"SYS_5V",8:"GND"}
        for ref,x,label in (("J9",25,"CO2"),("J10",53,"VOC-NOx"),("J11",81,"PRESSURE")):
            p(ref,f"AIR-SLOT {label}","Connector_PinHeader_2.54mm","PinHeader_2x04_P2.54mm_Vertical",x,98,0,slot_pins)
        p("C30","220u 10V","Capacitor_SMD","CP_Elec_8x10",128,94,0,{1:"SYS_5V",2:"GND"})
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
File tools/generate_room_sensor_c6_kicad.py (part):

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    add_passive(b,"C7","C",(175,82),"10u 10V","Capacitor_SMD:C_0805_2012Metric",{"1":"SYS_5V","2":"GND"})
    add_passive(b,"C8","C",(190,82),"22u 6.3V","Capacitor_SMD:C_0805_2012Metric",{"1":"+3V3","2":"GND"})

    c6_nets={"1":"GND","2":"+3V3","3":"C6_EN","4":"EXP_GPIO4","5":"EXP_GPIO5",
        "6":"I2C_SDA","7":"I2C_SCL","10":"STATUS_LED","13":"USB_D-","14":"USB_D+",
        "15":"C6_BOOT","21":"ONEWIRE","24":"RS485_RX","25":"RS485_TX","27":"RS485_DE",
        "28":"GND","29":"GND"}
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        value="EXPANSION / LED_EN / RELAY" if air_r2 else "EXPANSION",
        footprint="Connector_JST:JST_SH_SM08B-SRSS-TB_1x08-1MP_P1.00mm_Horizontal",datasheet="~",
        nets={"1":"+3V3","2":"GND","3":"I2C_SDA","4":"I2C_SCL","5":"ONEWIRE",
              "6":"EXP_GPIO4","7":"EXP_GPIO5","8":"SYS_5V"})
    add_passive(b,"LED1","LED",(195,180),"STATUS GREEN","LED_SMD:LED_0603_1608Metric",
                {"1":"GND","2":"STATUS_LED_R"} if air_r2 else {"1":"STATUS_LED_R","2":"GND"})
    add_passive(b,"R13","R",(180,180),"1k","Resistor_SMD:R_0603_1608Metric",{"1":"STATUS_LED","2":"STATUS_LED_R"})
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            ("R16",(270,210),"CONTACT1_EXT","CONTACT1"),
            ("R17",(290,210),"CONTACT2_EXT","CONTACT2"),
        ): add_passive(b,ref,"R",center,"1k","Resistor_SMD:R_0603_1608Metric",{"1":external,"2":gpio})
        for ref, center, gpio in (("R18",(270,225),"CONTACT1"),("R19",(290,225),"CONTACT2")):
            add_passive(b,ref,"R",center,"10k","Resistor_SMD:R_0603_1608Metric",{"1":"+3V3","2":gpio})
        for ref, center, gpio in (("C19",(270,240),"CONTACT1"),("C20",(290,240),"CONTACT2")):
            add_passive(b,ref,"C",center,"100n","Capacitor_SMD:C_0603_1608Metric",{"1":gpio,"2":"GND"})
        for ref, center, external in (("TVS3",(270,255),"CONTACT1_EXT"),("TVS4",(290,255),"CONTACT2_EXT")):
            add_passive(b,ref,"D_TVS",center,"PCESD3V3D3","Diode_SMD:D_SOD-323",{"1":"GND","2":external})
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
